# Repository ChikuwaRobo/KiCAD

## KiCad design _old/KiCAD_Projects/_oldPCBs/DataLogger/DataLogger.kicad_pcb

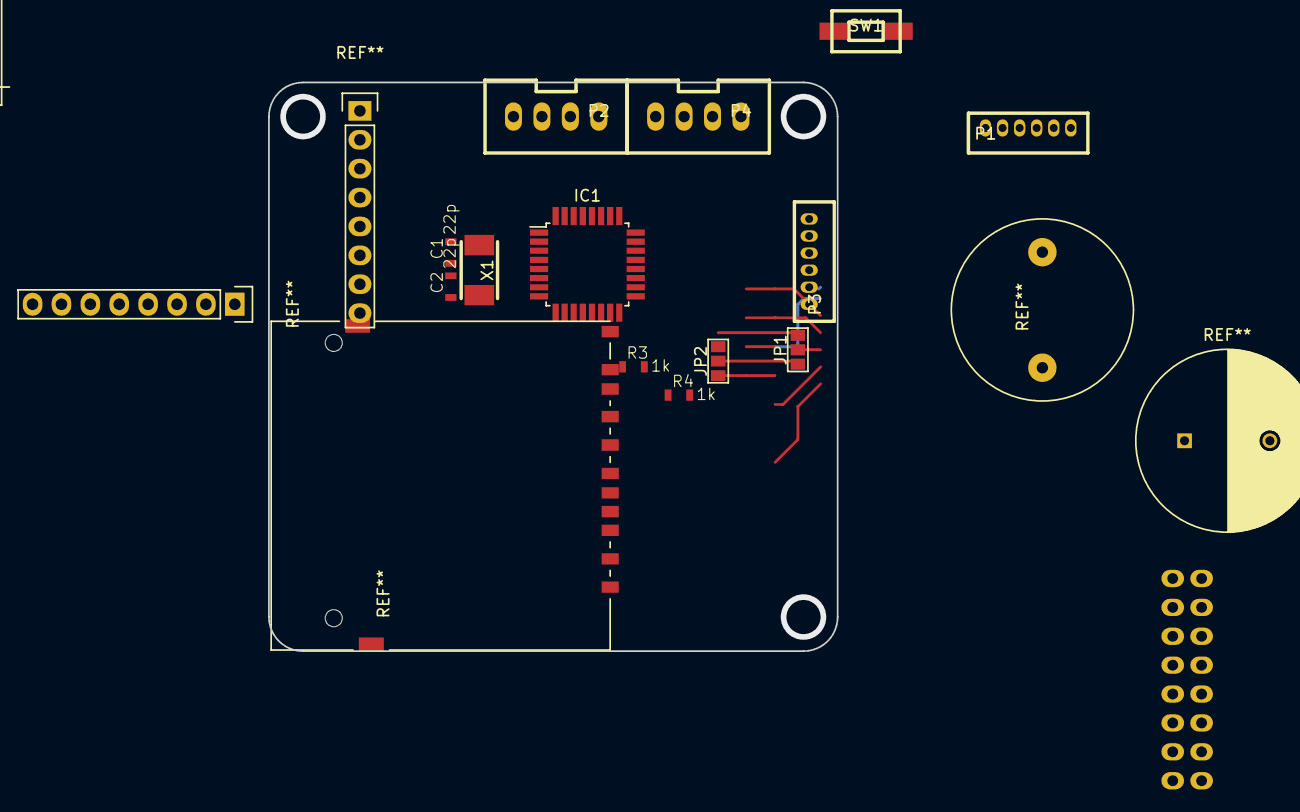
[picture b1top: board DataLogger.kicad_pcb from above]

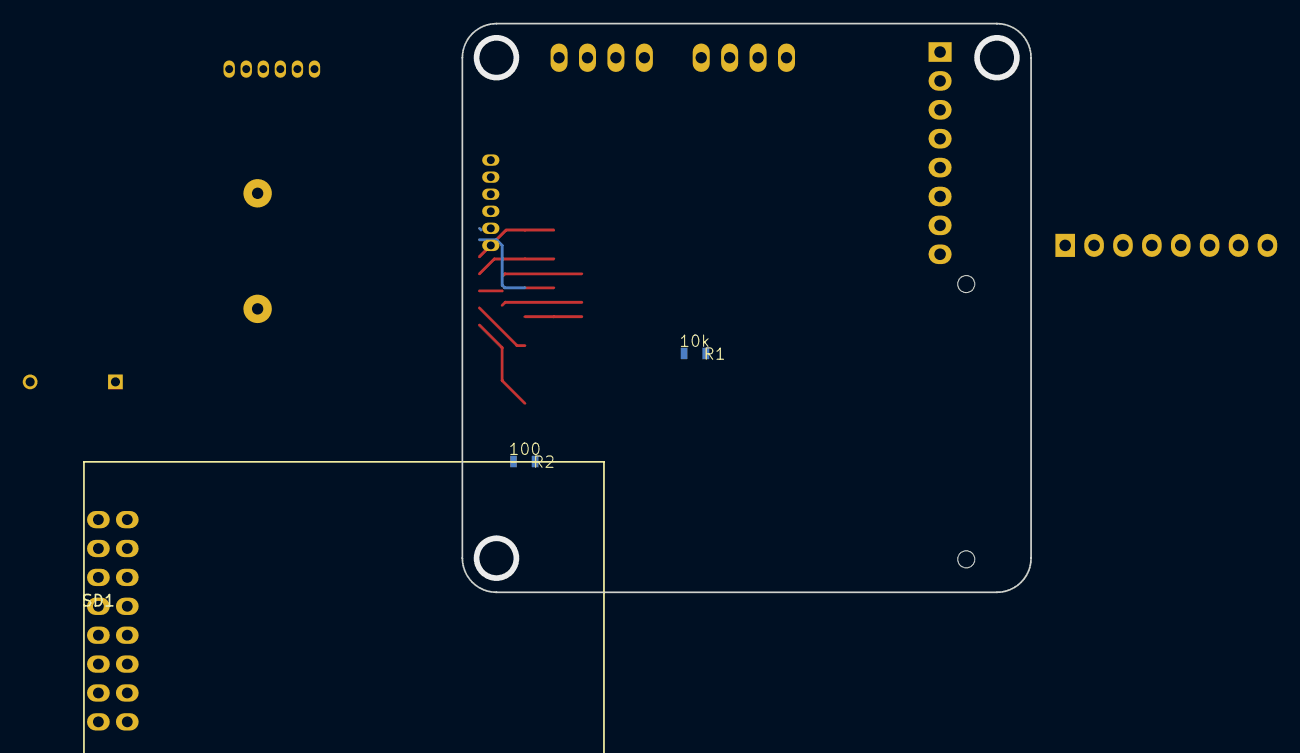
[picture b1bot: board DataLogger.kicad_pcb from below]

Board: 2 copper layers, 50.0 x 50.0 mm, 16 parts (3 on the bottom side), 18 nets.

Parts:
C1, C2: 22p; C1608_WP_S
IC1: ATMEGA328P-A; TQFP-32_7x7mm_Pitch0.8mm
JP1, JP2: JUMPER3; GS3
P1, P3: CONN_01X06; ZH_6T
P2, P4: CONN_01X04; XA_4T
R1: 10k; C1608_WP_S
R2: 100; C1608_WP_S
R3, R4: 1k; C1608_WP_S
SD1: SD_module
SW1: SW_PUSH; RP_SMD_Button
X1: CRYSTAL; ABM3_2pads

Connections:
+5V: IC1.4, IC1.6, IC1.18, IC1.20, P1.2, P2.2, P3.2, P4.2, SD1.3
/I2C_SCL: IC1.28, P4.3
/I2C_SDA: IC1.27, P4.4
/MISO: IC1.16, P3.5, SD1.7
/MOSI: IC1.15, P3.6, SD1.5
/RESET: IC1.29, JP1.3, P1.3, R1.2, R2.2
/RX: IC1.30, P1.6, R4.1
/SCK: IC1.17, P3.4, SD1.6
/SS0: IC1.14, JP2.1, SD1.4
/SS1: IC1.2, JP2.3
/TX: IC1.31, P1.5, P2.4, R3.1
GND: C1.1, C2.1, IC1.3, IC1.5, IC1.21, P1.1, P2.1, P3.1, P4.1, SD1.1, SD1.8, SW1.2
unnamed: C1.2, IC1.7, X1.2
unnamed: C2.2, IC1.8, X1.1
unnamed: JP1.1, JP2.2
unnamed: JP1.2, P3.3
unnamed: P2.3, R4.2
unnamed: R2.1, SW1.1

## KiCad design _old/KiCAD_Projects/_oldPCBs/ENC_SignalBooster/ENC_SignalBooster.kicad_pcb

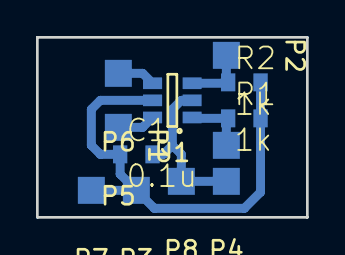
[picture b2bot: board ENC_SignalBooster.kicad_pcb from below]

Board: 2 copper layers, 15.0 x 10.0 mm, 12 parts (12 on the bottom side), 6 nets.

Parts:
C1: 0.1u; C1608_WP
P1, P2, P3, P4, P5, P6, P7, P8: CONN_01X01; Measurement_Point_Square-SMD-Pad_Small
R1, R2: 1k; C1608_WP
U1: SN74LVC2G14; SOT-23-6

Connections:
+5V: C1.1, P3.1, P7.1, R1.2, R2.2, U1.5
/ENC_A: P1.1, R1.1, U1.1
/ENC_B: P2.1, R2.1, U1.3
/OUT_A: P5.1, U1.6
/OUT_B: P6.1, U1.4
GND: C1.2, P4.1, P8.1, U1.2

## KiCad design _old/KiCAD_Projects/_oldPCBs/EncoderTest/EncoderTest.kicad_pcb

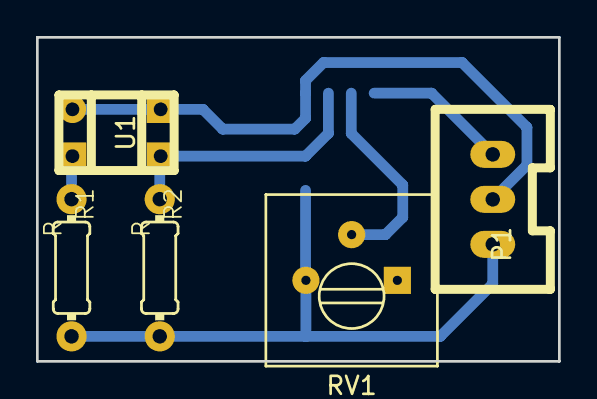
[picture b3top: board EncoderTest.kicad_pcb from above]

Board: 2 copper layers, 29.0 x 18.0 mm, 6 parts (1 on the bottom side), 6 nets.

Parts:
P1: CONN_01X03; XA_3T
R1, R2: R; 0204_2f7
RV1: POT; Potentiometer_Trimmer-Suntan-TSR-3386P
U1: FODM3011; Photointerrupter_64x42
U2: LM324; SOIC-14_3.9x8.7mm_Pitch1.27mm

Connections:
+5V: P1.2, U1.1, U1.4, U2.4
GND: P1.1, R1.2, R2.2, RV1.3, U2.11
unnamed: P1.3, U2.7
unnamed: R1.1, U1.2
unnamed: R2.1, U1.3, U2.5
unnamed: RV1.2, U2.6

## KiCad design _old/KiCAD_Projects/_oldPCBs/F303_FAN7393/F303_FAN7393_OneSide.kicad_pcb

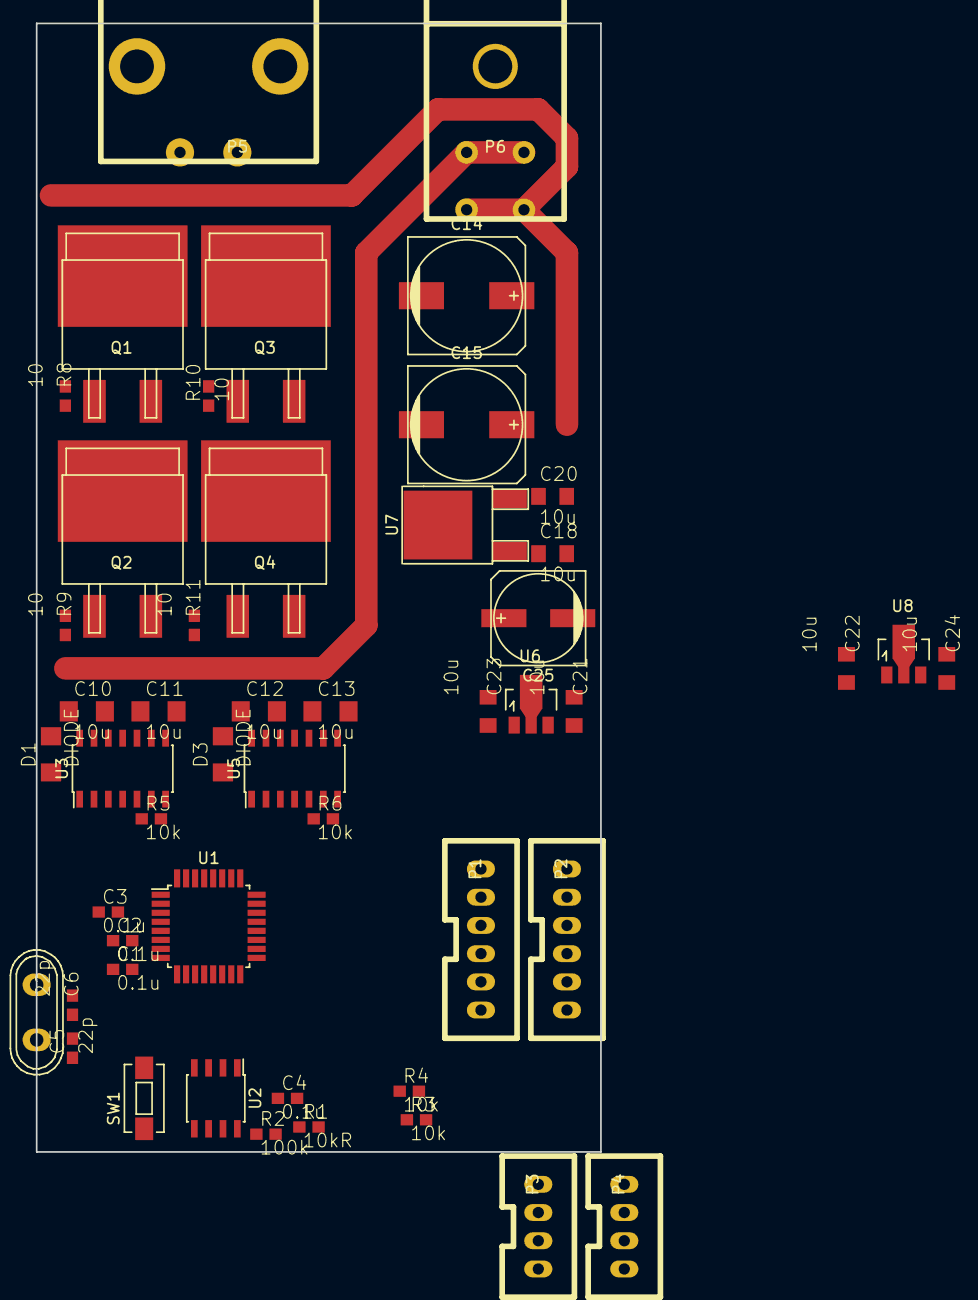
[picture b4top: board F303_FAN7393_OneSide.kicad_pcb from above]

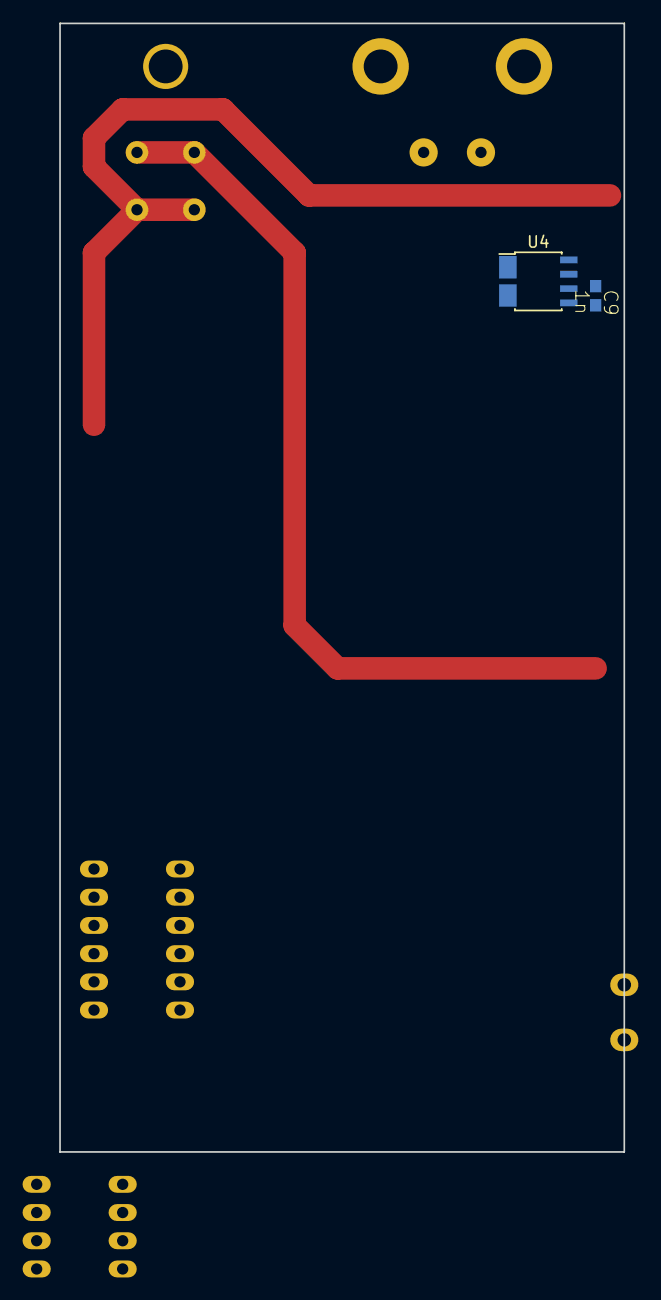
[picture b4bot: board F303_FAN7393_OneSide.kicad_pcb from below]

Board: 2 copper layers, 50.0 x 100.0 mm, 52 parts (2 on the bottom side), 44 nets.

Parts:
C1, C2, C3, C4: 0.1u; C1608
C5, C6: 22p; C1608
C9: 1n; C1608
C10, C11, C12, C13: 10u; C3216
C14, C15: 470u; c_elec_10x10.5
C18, C20, C21, C22, C23, C24: 10u; C2012
C25: 220u; c_elec_8x6.5
D1, D3: DIODE; C3216
P1, P2: CONN_01X06; XA_6T
P3, P4: CONN_01X04; XA_4T
P5: CONN_01X02; D-3200S_2L
P6: CONN_01X04; D-3500D_4S
Q1, Q2, Q3, Q4: MOSFET_N; D2-PAK
R1: 10kR; C1608
R2: 100k; C1608
R3, R4, R5, R6: 10k; C1608
R8, R9, R10, R11: 10; C1608
SW1: SW_PUSH; SW_SPST_EVQPE1
U1: STM32F303K8; TQFP-32_7x7mm_Pitch0.8mm
U2: MCP2551; SOIC-8_3.9x4.9mm_Pitch1.27mm
U3, U5: FAN7393; SOIC-14_3.9x8.7mm_Pitch1.27mm
U4: ACS714; SOIC-8_3.9x4.9mm_Pitch1.27mm_ACS
U6: NCP1117ST50T3G; SOT89-3_Housing
U7: MC78L15ACP; TO-252-2Lead
U8: NCP1117ST33T3G; SOT89-3_Housing
X1: CRYSTAL; Crystal_HC50-U_Vertical

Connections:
+3.3V: C1.1, C2.1, C3.1, C24.1, P1.2, R1.2, R3.1, R4.1, U1.1, U1.5, U1.17, U8.2
+5V: C22.1, C23.1, P3.2, U2.3, U4.8, U6.2, U8.3
+12V: P2.2, P4.2
+BATT: C14.1, C15.1, C18.1, P6.2, P6.4, Q1.D, Q3.D, U7.1
/CAN_RX: U1.21, U2.4
/CAN_TX: U1.22, U2.1
/ENC_A: P3.3, P3.4, R3.2, R4.2, U1.12
/GD_PS: C11.1, C13.1, D1.1, D3.1, U3.7, U5.7
/GP_PS: C20.1, C21.1, C25.1, U6.3, U7.3
/OUT_A: P5.1, U4.3, U4.4
/OUT_A_CS: C10.2, Q1.S, Q2.D, U3.11, U4.1, U4.2
/OUT_B: C12.2, P5.2, Q3.S, Q4.D, U5.11
/PWM_A: U1.6, U3.1
/PWM_B: U1.7, U5.1
/SPI1_MISO: P2.4, U1.27
/SPI1_MOSI: P2.3, U1.28
/SPI1_NSS: P2.6, U1.25
/SPI1_SCK: P2.5, U1.26
/USART1_RX: P1.6, U1.30
/USART1_TX: P1.5, U1.29
/~SD: U3.2, U5.2
GND: C1.2, C2.2, C3.2, C4.1, C5.2, C6.2, C9.2, C21.2, C22.2, C23.2, C24.2, P1.1, P2.1, P3.1, P4.1, R2.1, R5.2, R6.2, SW1.1, U1.16, U1.31, U1.32, U2.2, U3.3, U4.5, U5.3, U6.1, U8.1
GNDPWR: C11.2, C13.2, C14.2, C15.2, C18.2, C20.2, C25.2, P6.1, P6.3, Q2.S, Q4.S, U3.5, U5.5, U7.2
unnamed: C4.2, R1.1, SW1.2, U1.4
unnamed: C5.1, U1.3, X1.1
unnamed: C6.1, U1.2, X1.2
unnamed: C9.1, U4.6
unnamed: C10.1, D1.2, U3.13
unnamed: C12.1, D3.2, U5.13
unnamed: P1.3, U1.24
unnamed: P1.4, U1.23
unnamed: P4.3, U2.6
unnamed: P4.4, U2.7
unnamed: Q1.G, R8.1
unnamed: Q2.G, R9.1
unnamed: Q3.G, R10.1
unnamed: Q4.G, R11.1
unnamed: R2.2, U2.8
unnamed: R5.1, U3.4
unnamed: R6.1, U5.4
unnamed: R8.2, U3.12
unnamed: R9.2, U3.6
unnamed: R10.2, U5.12
unnamed: R11.2, U5.6

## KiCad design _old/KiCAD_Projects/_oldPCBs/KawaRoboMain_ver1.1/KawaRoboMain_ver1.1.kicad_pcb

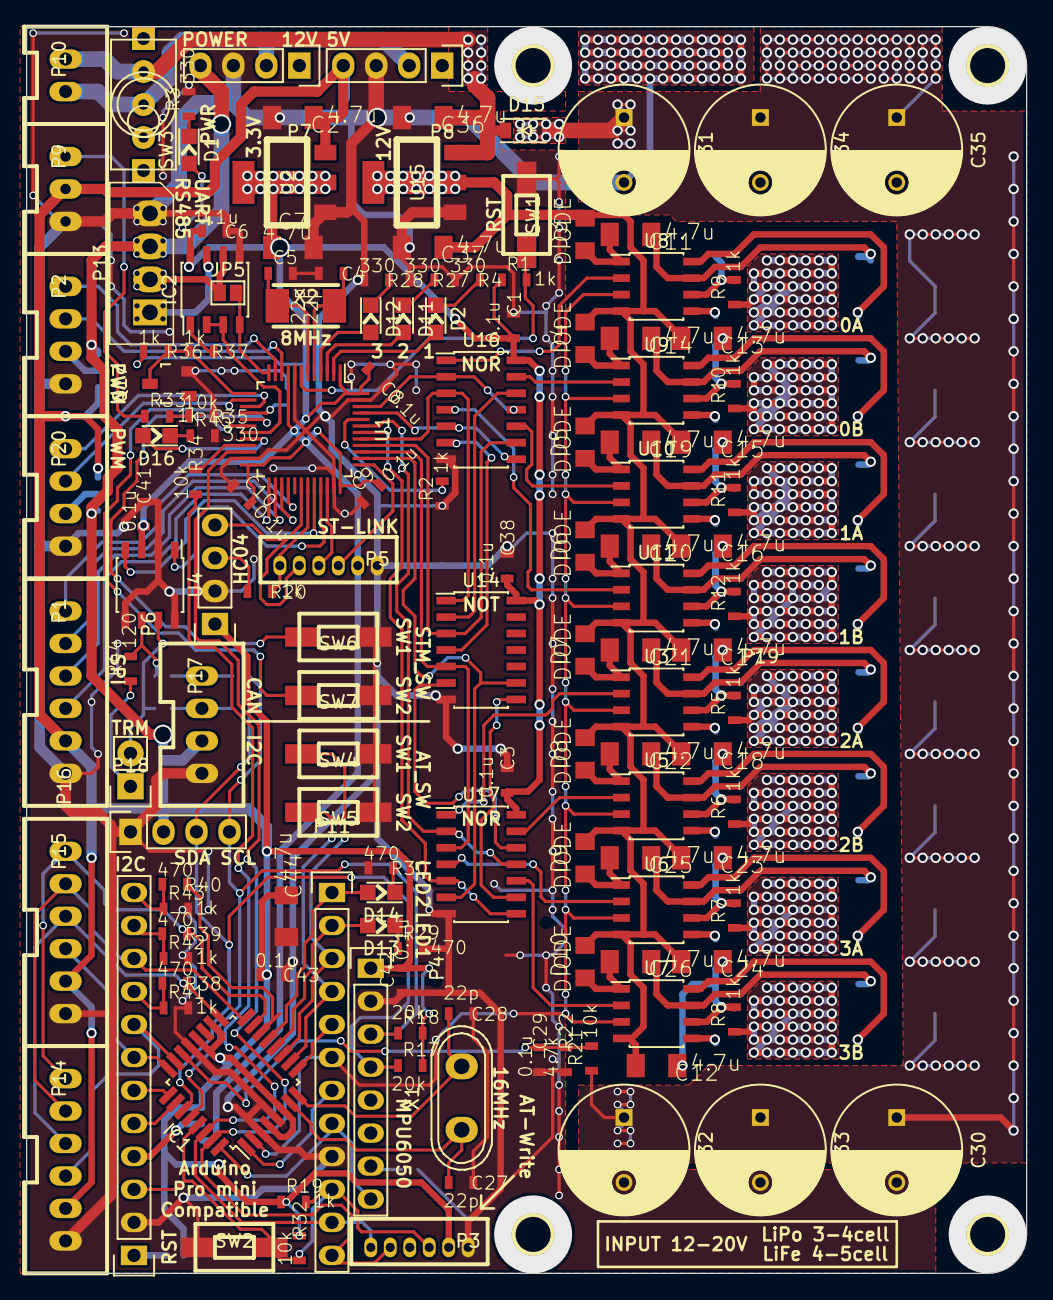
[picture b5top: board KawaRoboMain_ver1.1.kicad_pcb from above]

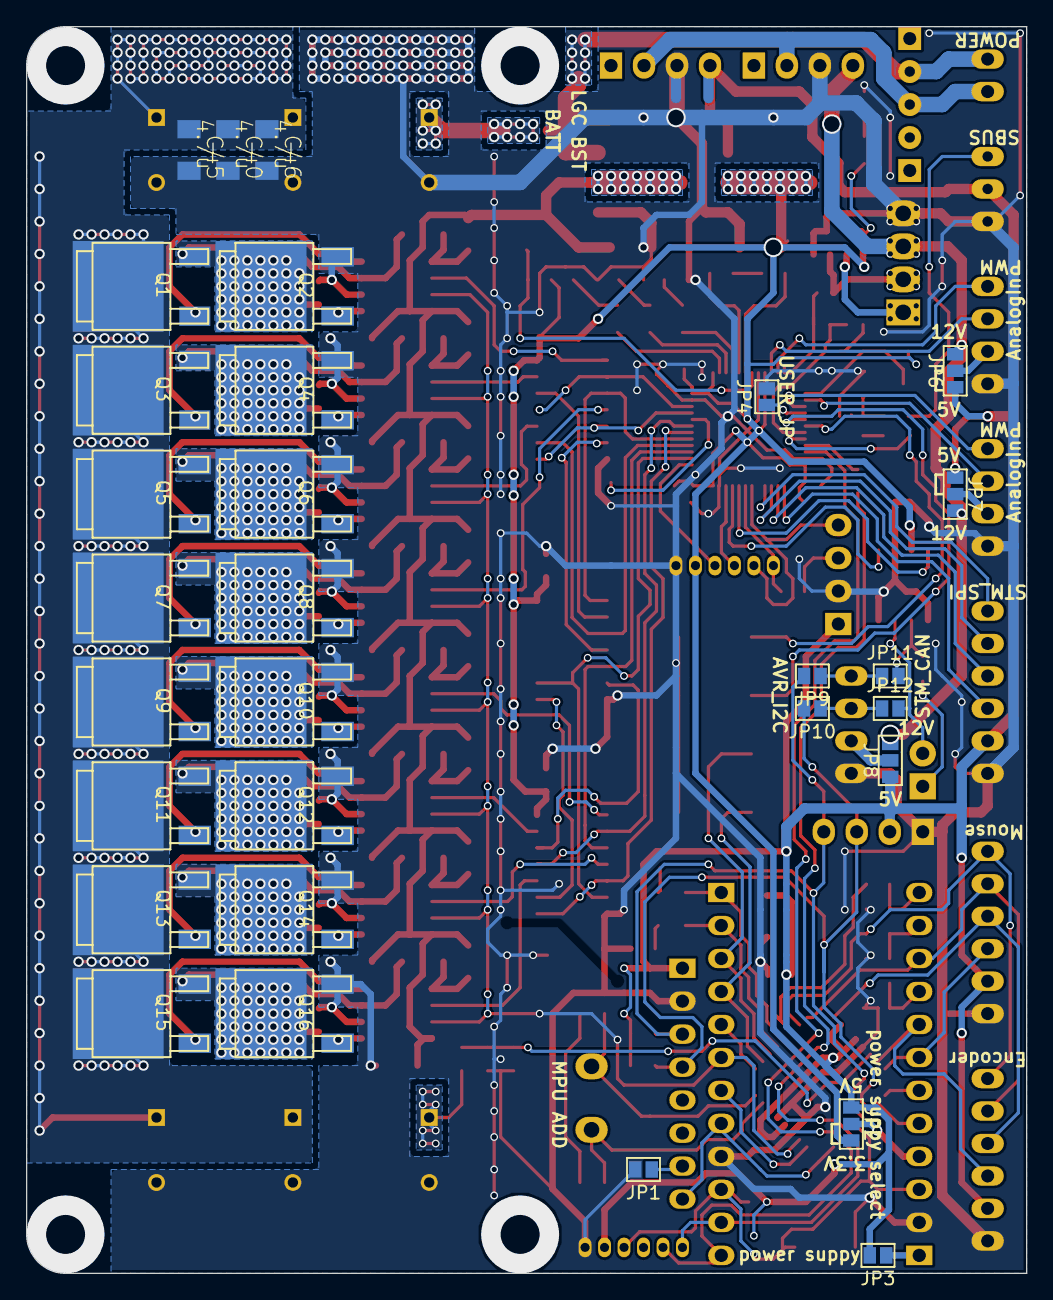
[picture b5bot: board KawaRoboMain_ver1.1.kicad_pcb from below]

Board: 2 copper layers, 77.0 x 96.0 mm, 174 parts (31 on the bottom side), 140 nets.

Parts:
C1, C3, C6, C8, C9, C10, C29, C38, C41, C42, C43: 0.1u; C1608_WP_S
C2, C7, C11, C12, C13, C14, C15, C16, C17, C18, C19, C20, C21, C22, C23, C24, C25, C26, C36, C37, C40, C44, C45, C46: 4.7u; C3216_S
C4, C5, C27, C28: 22p; C1608_WP_S
C30, C31, C32, C33, C34, C35: 220u; C_Radial_D10_L13_P5
D1, D2, D11, D12, D13, D14, D16: LED; LED_0805
D3, D4, D5, D6, D7, D8, D9, D10: DIODE; C2012
D15: DIODE; SOD-123
IC1: ATMEGA328P-A; TQFP-32_7x7mm_Pitch0.8mm
IC2: SP3485CN; SOIC-8_3.9x4.9mm_Pitch1.27mm_S
JP1, JP3, JP4, JP5, JP9, JP10, JP11, JP12: JUMPER; GS2
JP2, JP6, JP7, JP8: JUMPER3; GS3
P1, P14, P15: CONN_01X06; XA_6T
P2, P17, P20: CONN_01X04; XA_4T
P3, P5: CONN_01X06; ZH_6T
P4: CONN_01X08; Socket_Strip_Straight_1x08_MPU6050
P6, P7, P8, P18: CONN_01X04; Socket_Strip_Straight_1x04
P9: CONN_01X03; XA_3T
P10: CONN_01X02; XA_2T
P11, P12: CONN_01X12; Pin_Header_Straight_1x12
P13: CONN_01X04; Molex_SPOX-5267_22-03-5045_04x2.54mm_Straight
P16: CONN_01X02; Socket_Strip_Straight_1x02
P19: CONN_01X01; KawaRobo_Headsink
P21: CONN_01X01; kw
P22: CONN_01X01; ckw
Q1, Q2, Q3, Q4, Q5, Q6, Q7, Q8, Q9, Q10, Q11, Q12, Q13, Q14, Q15, Q16: MOSFET_N; SOT-428_GDS_compact
Q17: MOSFET_N; SOT-23_Handsoldering
R1, R2, R5, R6, R7, R8, R9, R10, R11, R12, R19, R20, R33, R36, R37, R41, R42, R43: 1k; C1608_WP_S
R3, R4, R27, R28, R45: 330; C1608_WP_S
R17, R18: 20k; C1608_WP_S
R21, R32, R34, R35: 10k; C1608_WP_S
R22: 4.7k; C1608_WP_S
R29, R30, R38, R39, R40: 470; C1608_WP_S
R44: 120; C1608_WP_S
SW1, SW2, SW4, SW5, SW6, SW7: SW_PUSH; RP_SMD_Button
SW3: SWITCH_INV; SW_toggle_3P
U1: STM32F103_48; LQFP-48_7x7mm_Pitch0.5mm
U2: NCP1117ST33T3G; SOT-223_reg
U3, U5, U6, U7, U8, U9, U10, U11: NCP5359; SOIC-8_3.9x4.9mm_Pitch1.27mm_S
U4: MAX3051; SOIC-8_3.9x4.9mm_Pitch1.27mm_S
U14: 74HC04; SOIC-14_3.9x8.7mm_Pitch1.27mm
U15: NCP1117ST12T3G; SOT-223_reg
U16, U17: 74HC02; SOIC-14_3.9x8.7mm_Pitch1.27mm
X1: CRYSTAL; Crystal_HC50-U_Vertical
X2: CRYSTAL; ABM3_2pads

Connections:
+3.3V: C1.2, C3.2, C6.2, C7.1, C8.2, C9.2, C10.2, C38.2, C41.2, D1.1, IC2.8, JP2.3, P5.2, R1.1, R36.2, U1.1, U1.9, U1.24, U1.36, U1.48, U2.2, U4.3, U14.14, U16.14, U17.14
+5V: C2.1, C42.2, C43.2, C44.1, IC1.4, IC1.6, IC1.18, IC1.20, JP2.1, JP3.2, JP6.1, JP7.1, JP8.1, P1.2, P3.2, P4.1, P6.1, P8.4, P9.2, P14.2, P15.2, P18.2, R17.2, R18.2, R19.1, R32.1, U2.3
+12V: JP6.3, JP7.3, JP8.3, P7.4, P13.3
+BATT: C30.1, C31.1, C32.1, C33.1, C34.1, C35.1, C40.1, C45.1, C46.1, D15.2, Q1.D, Q3.D, Q5.D, Q7.D, Q9.D, Q11.D, Q13.D, Q15.D, R21.1
/AT_A2: IC1.25, P12.6
/AT_A3: IC1.26, P12.5
/AT_LED1: D13.1, IC1.12, P11.2
/AT_LED2: D14.1, IC1.13, P11.1
/AT_RST: IC1.29, P3.3, P11.10, P12.3, R19.2, R32.2, SW2.2
/AT_RX: IC1.30, P3.6, P11.11, R34.2
/AT_SW1: IC1.11, P11.3, SW4.2
/AT_SW2: IC1.10, P11.4, SW5.2
/AT_TX: IC1.31, P3.5, P11.12, U1.22
/BOOT0: R2.2, U1.44
/BUZZER: IC1.9, P11.5
/CAN_RX: U1.32, U4.4
/CAN_TX: U1.33, U4.1
/GD_12V: C12.2, C13.2, C15.2, C16.2, C17.2, C18.2, C23.2, C24.2, C37.1, D3.2, D4.2, D5.2, D6.2, D7.2, D8.2, D9.2, D10.2, U3.4, U5.4, U6.4, U7.4, U8.4, U9.4, U10.4, U11.4, U15.2
/I2C_SCL: IC1.28, JP9.2, P4.3, P18.4, R18.1
/I2C_SDA: IC1.27, JP10.2, P4.4, P18.3, R17.1
/INT0: IC1.32, P4.8, P11.8
/INT1: IC1.1, P11.7
/LOGIC_BATT: C36.1, D15.1, P10.2, SW3.1, U15.3
/Motor0CW: U1.41, U14.1, U16.3
/Motor0PWM: U1.46, U16.2, U16.11
/Motor1CW: U1.40, U14.3, U16.9
/Motor1PWM: U1.45, U16.5, U16.8
/Motor2CW: U1.39, U14.5, U17.3
/Motor2PWM: U1.43, U17.2, U17.11
/Motor3CW: U1.38, U14.9, U17.6
/Motor3PWM: U1.42, U17.5, U17.8
/Motor~SD: IC1.2, P11.6, U3.3, U5.3, U6.3, U7.3, U8.3, U9.3, U10.3, U11.3
/NRST: R1.2, SW1.2, U1.7
/OSC_IN: C4.1, U1.5, X2.1
/OSC_OUT: C5.1, U1.6, X2.2
/OUT_0_A: C11.1, Q1.S, Q2.D, R9.1, U8.7
/OUT_0_B: C14.1, Q3.S, Q4.D, R10.1, U9.7
/OUT_1_A: C19.1, Q5.S, Q6.D, R11.1, U10.7
/OUT_1_B: C20.1, Q7.S, Q8.D, R12.1, U11.7
/OUT_2_A: C21.1, Q9.S, Q10.D, R5.1, U3.7
/OUT_2_B: C22.1, Q11.S, Q12.D, R6.1, U5.7
/OUT_3_A: C25.1, Q13.S, Q14.D, R7.1, U6.7
/OUT_3_B: C26.1, Q15.S, Q16.D, R8.1, U7.7
/PWM_0_A: U8.2, U16.1
/PWM_0_B: U9.2, U16.13
/PWM_1_A: U10.2, U16.10
/PWM_1_B: U11.2, U16.4
/PWM_2_A: U3.2, U17.1
/PWM_2_B: U5.2, U17.13
/PWM_3_A: U6.2, U17.4
/PWM_3_B: U7.2, U17.10
/PWM_T2C1: P2.3, U1.10
/PWM_T2C2: P2.4, U1.11
/PWM_T3C1: P20.3, U1.14
/PWM_T3C2: P20.4, U1.15
/RAW: JP3.1, P12.1
/SBUS: P9.3, R33.1
/SERVO_DIR: IC2.2, IC2.3, U1.19
/SERVO_RX: Q17.D, R36.1, R37.2, U1.13
/SERVO_TX: IC2.4, JP5.2, U1.12
/SPI_MISO: IC1.16, P12.10, P14.5, P15.5
/SPI_MOSI: IC1.15, P14.6, P15.6, R39.1
/SPI_SCK: IC1.17, P14.4, P15.4, R38.1
/SPI_SS_ENC: IC1.23, P12.8, P14.3
/SPI_SS_Mouse: IC1.24, P12.7, P15.3
/SPI_SS_USB: IC1.14, R40.1
/STM_LED1: D2.1, U1.2
/STM_LED2: D11.1, U1.3
/STM_LED3: D12.1, U1.4
/STM_LED4: D16.1, U1.20
/STM_MISO: P1.5, U1.27
/STM_MOSI: P1.6, U1.28
/STM_SCK: P1.4, U1.26
/STM_SW1: SW6.2, U1.18
/STM_SW2: SW7.2, U1.17
/STM_~SS0: P1.3, U1.25
/SWCLK: P5.3, U1.37
/SWDIO: P5.4, U1.34
/USART_RX: P5.6, R20.1, U1.31
/USART_TX: P5.5, P6.4, U1.30
/batt_voltage: C29.1, IC1.22, R21.2, R22.1
GND: C1.1, C2.2, C3.1, C4.2, C5.2, C6.1, C7.2, C8.1, C9.1, C10.1, C12.1, C13.1, C15.1, C16.1, C17.1, C18.1, C23.1, C24.1, C27.1, C28.1, C29.2, C30.2, C31.2, C32.2, C33.2, C34.2, C35.2, C36.2, C37.2, C38.1, C40.2, C41.1, C42.1, C43.1, C44.2, C45.2, C46.2, IC1.3, IC1.5, IC1.21, IC2.5, JP1.2, JP4.2, P1.1, P2.1, P3.1, P4.2, P5.1, P6.2, P7.3, P8.3, P9.1, P11.9, P12.2, P13.4, P14.1, P15.1, P17.1, P18.1, P20.1, Q2.S, Q4.S, Q6.S, Q8.S, Q10.S, Q12.S, Q14.S, Q16.S, Q17.S, R2.1, R3.2, R4.2, R5.2, R6.2, R7.2, R8.2, R9.2, R10.2, R11.2, R12.2, R22.2, R27.2, R28.2, R29.2, R30.2, R35.1, R41.2, R42.2, R43.2, R45.2, SW1.1, SW2.1, SW4.1, SW5.1, SW6.1, SW7.1, U1.8, U1.23, U1.35, U1.47, U2.1, U3.6, U4.2, U4.5, U4.8, U5.6, U6.6, U7.6, U8.6, U9.6, U10.6, U11.6, U14.7, U15.1, U16.7, U17.7
unnamed: C11.2, D3.1, U8.1
unnamed: C14.2, D4.1, U9.1
unnamed: C19.2, D5.1, U10.1
unnamed: C20.2, D6.1, U11.1
unnamed: C21.2, D7.1, U3.1
unnamed: C22.2, D8.1, U5.1
unnamed: C25.2, D9.1, U6.1
unnamed: C26.2, D10.1, U7.1
unnamed: C27.2, IC1.7, X1.1
unnamed: C28.2, IC1.8, X1.2
unnamed: D1.2, R3.1
unnamed: D2.2, R4.1
unnamed: D11.2, R27.1
unnamed: D12.2, R28.1
unnamed: D13.2, R29.1
unnamed: D14.2, R30.1
unnamed: D16.2, R45.1
unnamed: IC2.1, R37.1
unnamed: IC2.6, JP5.1, P13.2
unnamed: IC2.7, P13.1
unnamed: JP1.1, P4.7
unnamed: JP2.2, P12.4
unnamed: JP4.1, U1.16
unnamed: JP6.2, P2.2
unnamed: JP7.2, P20.2
unnamed: JP8.2, P17.2
unnamed: JP10.1, JP12.1, P17.3
unnamed: JP9.1, JP11.1, P17.4
unnamed: JP11.2, R44.2, U4.6
unnamed: JP12.2, P16.2, U4.7
unnamed: P6.3, R20.2
unnamed: P7.2, P8.2, P10.1, SW3.2
unnamed: P12.9, R38.2, R41.1
unnamed: P12.11, R39.2, R42.1
unnamed: P12.12, R40.2, R43.1
unnamed: P16.1, R44.1
unnamed: Q1.G, U8.8
unnamed: Q2.G, U8.5
unnamed: Q3.G, U9.8
unnamed: Q4.G, U9.5
unnamed: Q5.G, U10.8
unnamed: Q6.G, U10.5
unnamed: Q7.G, U11.8
unnamed: Q8.G, U11.5
unnamed: Q9.G, U3.8
unnamed: Q10.G, U3.5
unnamed: Q11.G, U5.8
unnamed: Q12.G, U5.5
unnamed: Q13.G, U6.8
unnamed: Q14.G, U6.5
unnamed: Q15.G, U7.8
unnamed: Q16.G, U7.5
unnamed: Q17.G, R33.2, R35.2
unnamed: R34.1, U1.21
unnamed: U14.2, U16.12
unnamed: U14.4, U16.6
unnamed: U14.6, U17.12
unnamed: U14.8, U17.9
